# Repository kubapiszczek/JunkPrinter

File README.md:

# JunkPrinter
My junky 3d printer data
- klipper config
- main board kicad files

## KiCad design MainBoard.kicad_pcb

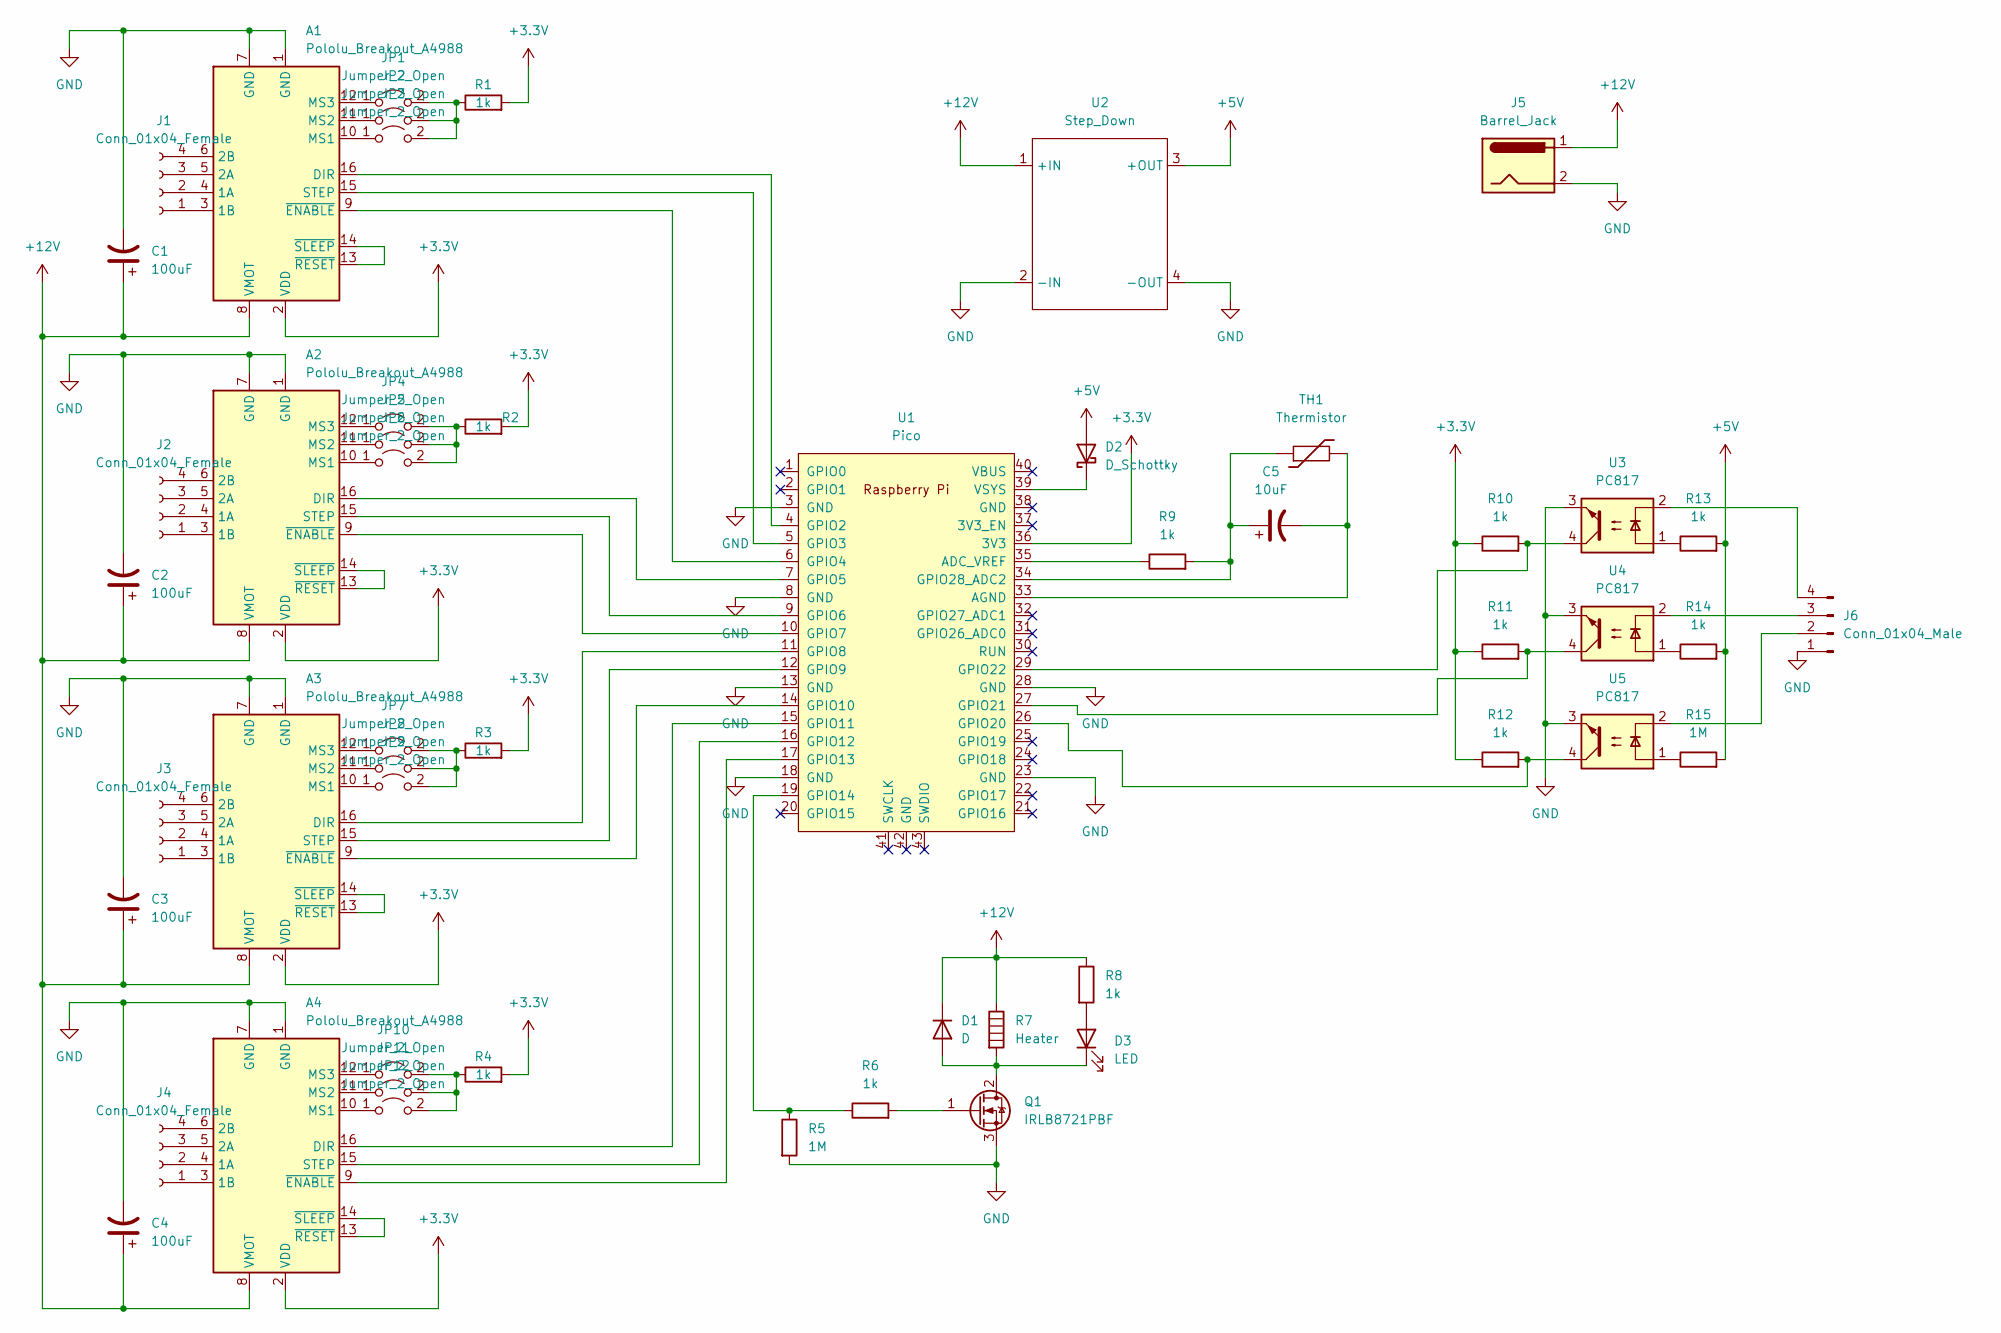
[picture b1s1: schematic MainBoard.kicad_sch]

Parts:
A1, A2, A3, A4: Pololu_Breakout_A4988; Pololu_Breakout-16_15.2x20.3mm
C1, C2, C3, C4: 100uF; CP_Radial_D6.3mm_P2.50mm
C5: 10uF; CP_Radial_D5.0mm_P2.00mm
D1: D; D_DO-41_SOD81_P7.62mm_Horizontal
D2: D_Schottky; D_5KP_P10.16mm_Horizontal
D3: LED; LED_D3.0mm
J1, J2, J3, J4: Conn_01x04_Female; PinSocket_1x04_P2.54mm_Vertical
J5: Barrel_Jack; BarrelJack_Horizontal
J6: Conn_01x04_Male; PinHeader_1x04_P2.54mm_Vertical
JP1, JP2, JP3, JP4, JP5, JP6, JP7, JP8, JP9, JP10, JP11, JP12: Jumper_2_Open; PinHeader_1x02_P2.54mm_Vertical
Q1: IRLB8721PBF; TO-220-3_Vertical
R1, R2, R3, R4, R6, R8, R9, R10, R11, R12, R13, R14: 1k; R_Axial_DIN0207_L6.3mm_D2.5mm_P10.16mm_Horizontal
R5, R15: 1M; R_Axial_DIN0207_L6.3mm_D2.5mm_P10.16mm_Horizontal
R7: Heater; PinHeader_1x02_P2.54mm_Vertical
TH1: Thermistor; PinHeader_1x02_P2.54mm_Vertical
U1: Pico; RPi_Pico_SMD_TH
U2: Step_Down
U3, U4, U5: PC817; DIP-4_W7.62mm

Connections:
+3V3: A1.2 (VDD), A2.2 (VDD), A3.2 (VDD), A4.2 (VDD), R1.2, R2.2, R3.2, R4.2, R10.1, R11.1, R12.1, U1.36 (3V3)
+5V: D2.2 (A), R13.2, R14.2, R15.2, U2.3 (+OUT)
+12V: A1.8 (VMOT), A2.8 (VMOT), A3.8 (VMOT), A4.8 (VMOT), C1.1, C2.1, C3.1, C4.1, D1.1 (K), J5.1, R7.1, R8.1, U2.1 (+IN)
GND: A1.1 (GND), A1.7 (GND), A2.1 (GND), A2.7 (GND), A3.1 (GND), A3.7 (GND), A4.1 (GND), A4.7 (GND), C1.2, C2.2, C3.2, C4.2, J5.2, J6.1, Q1.3 (S), R5.2, U1.3 (GND), U1.8 (GND), U1.13 (GND), U1.18 (GND), U1.23 (GND), U1.28 (GND), U2.2 (-IN), U2.4 (-OUT), U3.3, U4.3, U5.3
unnamed: A1.3 (1B), J1.1
unnamed: A1.4 (1A), J1.2
unnamed: A1.5 (2A), J1.3
unnamed: A1.6 (2B), J1.4
unnamed: A1.9 (~ENABLE), U1.6 (GPIO4)
unnamed: A1.10 (MS1), JP3.1 (A)
unnamed: A1.11 (MS2), JP2.1 (A)
unnamed: A1.12 (MS3), JP1.1 (A)
unnamed: A1.13 (~RESET), A1.14 (~SLEEP)
unnamed: A1.15 (STEP), U1.5 (GPIO3)
unnamed: A1.16 (DIR), U1.4 (GPIO2)
unnamed: A2.3 (1B), J2.1
unnamed: A2.4 (1A), J2.2
unnamed: A2.5 (2A), J2.3
unnamed: A2.6 (2B), J2.4
unnamed: A2.9 (~ENABLE), U1.10 (GPIO7)
unnamed: A2.10 (MS1), JP6.1 (A)
unnamed: A2.11 (MS2), JP5.1 (A)
unnamed: A2.12 (MS3), JP4.1 (A)
unnamed: A2.13 (~RESET), A2.14 (~SLEEP)
unnamed: A2.15 (STEP), U1.9 (GPIO6)
unnamed: A2.16 (DIR), U1.7 (GPIO5)
unnamed: A3.3 (1B), J3.1
unnamed: A3.4 (1A), J3.2
unnamed: A3.5 (2A), J3.3
unnamed: A3.6 (2B), J3.4
unnamed: A3.9 (~ENABLE), U1.14 (GPIO10)
unnamed: A3.10 (MS1), JP9.1 (A)
unnamed: A3.11 (MS2), JP8.1 (A)
unnamed: A3.12 (MS3), JP7.1 (A)
unnamed: A3.13 (~RESET), A3.14 (~SLEEP)
unnamed: A3.15 (STEP), U1.12 (GPIO9)
unnamed: A3.16 (DIR), U1.11 (GPIO8)
unnamed: A4.3 (1B), J4.1
unnamed: A4.4 (1A), J4.2
unnamed: A4.5 (2A), J4.3
unnamed: A4.6 (2B), J4.4
unnamed: A4.9 (~ENABLE), U1.17 (GPIO13)
unnamed: A4.10 (MS1), JP12.1 (A)
unnamed: A4.11 (MS2), JP11.1 (A)
unnamed: A4.12 (MS3), JP10.1 (A)
unnamed: A4.13 (~RESET), A4.14 (~SLEEP)
unnamed: A4.15 (STEP), U1.16 (GPIO12)
unnamed: A4.16 (DIR), U1.15 (GPIO11)
unnamed: C5.1, R9.2, TH1.1, U1.34 (GPIO28_ADC2)
unnamed: C5.2, TH1.2, U1.33 (AGND)
unnamed: D1.2 (A), D3.1 (K), Q1.2 (D), R7.2
unnamed: D2.1 (K), U1.39 (VSYS)
unnamed: D3.2 (A), R8.2
unnamed: J6.2, U5.2
unnamed: J6.3, U4.2
unnamed: J6.4, U3.2
unnamed: JP1.2 (B), JP2.2 (B), JP3.2 (B), R1.1
unnamed: JP4.2 (B), JP5.2 (B), JP6.2 (B), R2.1
unnamed: JP7.2 (B), JP8.2 (B), JP9.2 (B), R3.1
unnamed: JP10.2 (B), JP11.2 (B), JP12.2 (B), R4.1
unnamed: Q1.1 (G), R6.2
unnamed: R5.1, R6.1, U1.19 (GPIO14)
unnamed: R9.1, U1.35 (ADC_VREF)
unnamed: R10.2, U1.29 (GPIO22), U3.4
unnamed: R11.2, U1.27 (GPIO21), U4.4
unnamed: R12.2, U1.26 (GPIO20), U5.4
unnamed: R13.1, U3.1
unnamed: R14.1, U4.1
unnamed: R15.1, U5.1

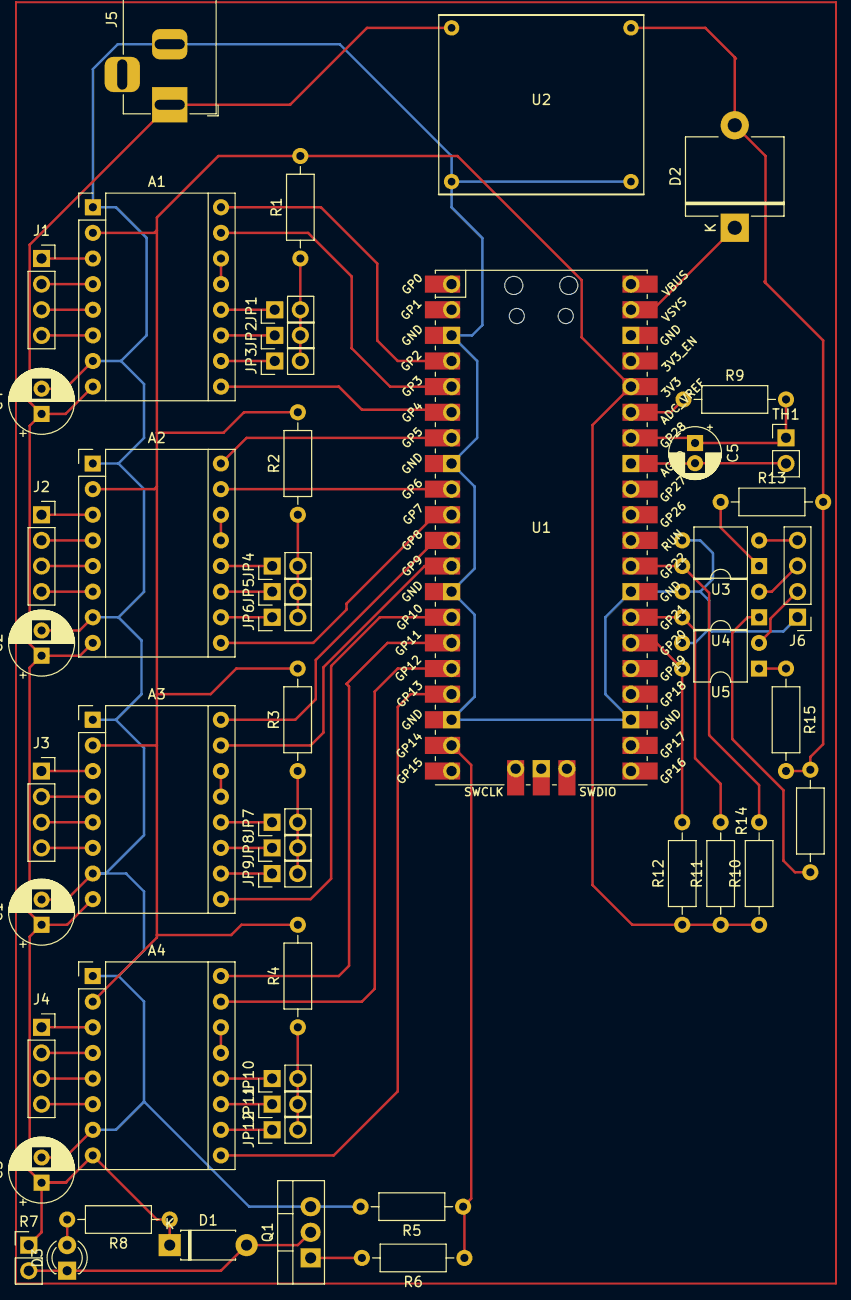
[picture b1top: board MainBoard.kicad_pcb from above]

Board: 2 copper layers, 52 parts (0 on the bottom side), 69 nets.
